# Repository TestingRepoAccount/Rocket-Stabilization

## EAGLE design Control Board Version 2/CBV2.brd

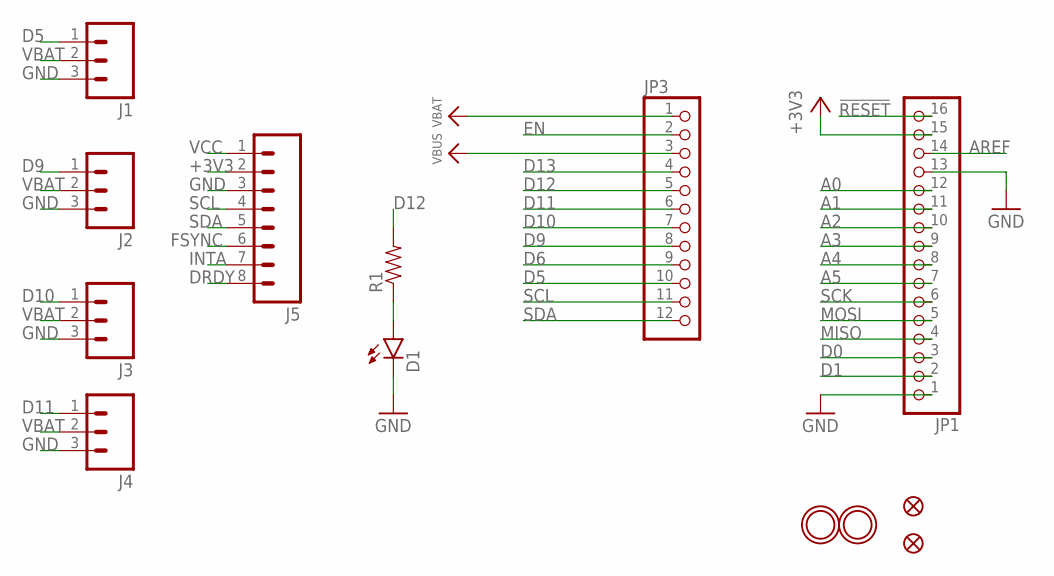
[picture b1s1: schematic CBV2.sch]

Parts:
D1: LED3MM
J1, J2, J3, J4: M03PTH; 1X03
J5: M08; 1X08_ROUND
JP1: HEADER-1X16ROUND; 1X16_ROUND
JP3: HEADER-1X12; 1X12_ROUND
R1: RESISTORPTH-1/4W; AXIAL-0.4
U$31, U$32: MOUNTINGHOLE2.5; MOUNTINGHOLE_2.5_PLATED
U$34, U$35: FIDUCIAL""; FIDUCIAL_1MM

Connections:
!RESET: JP1.16
+3V3: J5.2, JP1.15
A0: JP1.12
A1: JP1.11
A2: JP1.10
A3: JP1.9
A4: JP1.8
A5: JP1.7
AREF: JP1.14
D0: JP1.3
D1: JP1.2
D5: J1.1, JP3.10
D6: JP3.9
D9: J2.1, JP3.8
D10: J3.1, JP3.7
D11: J4.1, JP3.6
D12: JP3.5, R1.P$2 (2)
D13: JP3.4
DRDY: J5.8
EN: JP3.2
FSYNC: J5.6
GND: D1.K (C), J1.3, J2.3, J3.3, J4.3, J5.3, JP1.1, JP1.13
INTA: J5.7
MISO: JP1.4
MOSI: JP1.5
unnamed: D1.A, R1.P$1 (1)
SCK: JP1.6
SCL: J5.4, JP3.11
SDA: J5.5, JP3.12
VBAT: J1.2, J2.2, J3.2, J4.2, JP3.1
VBUS: JP3.3
VCC: J5.1

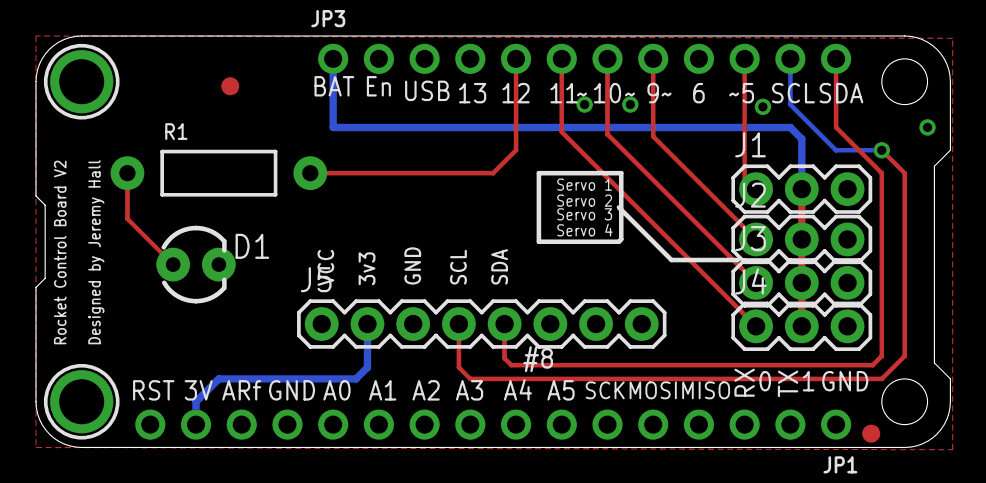
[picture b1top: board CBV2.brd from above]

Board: 2 copper layers, 50.8 x 22.9 mm, 13 parts (0 on the bottom side), 11 nets.

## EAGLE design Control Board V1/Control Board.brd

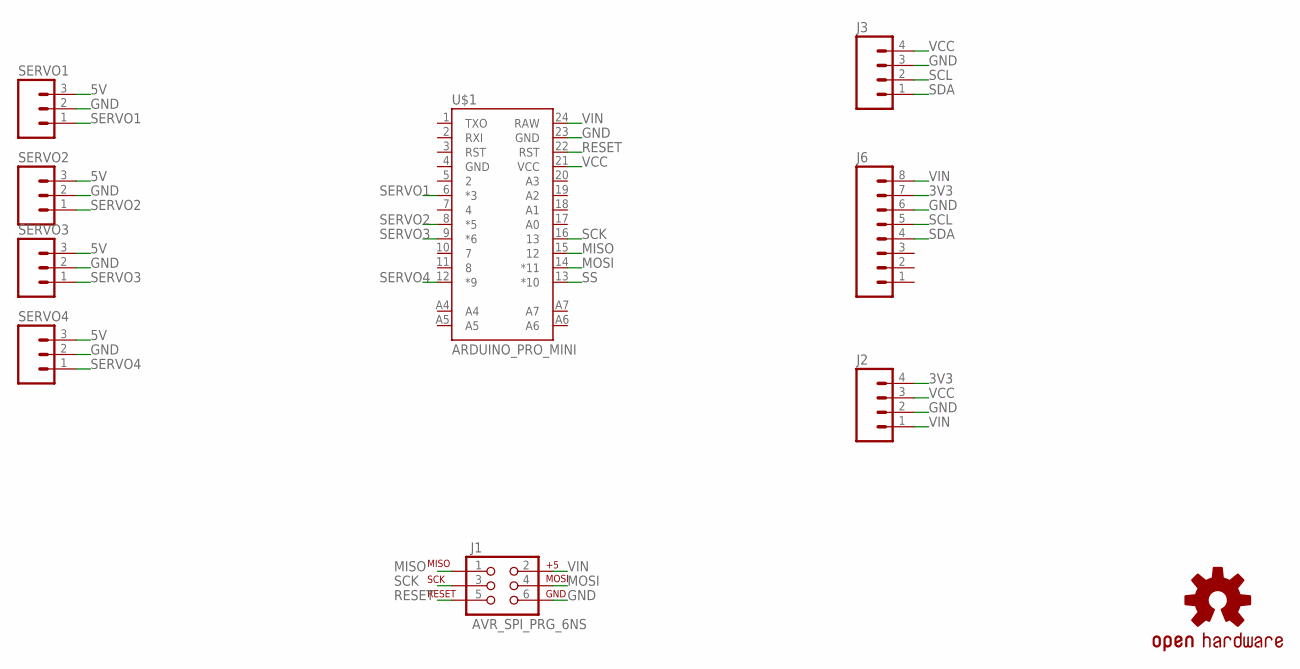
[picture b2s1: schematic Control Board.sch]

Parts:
J1: AVR_SPI_PRG_6NS; 2X3-NS
J2, J3: M04PTH; 1X04
J6: M08; 1X08_ROUND
LOGO1: OSHW-LOGOM-COPPER; OSHW-LOGO-M_COPPER
SERVO1, SERVO2, SERVO3, SERVO4: M03PTH; 1X03
U$1: ARDUINO_PRO_MINI

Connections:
3V3: J2.4, J6.7
5V: SERVO1.3, SERVO2.3, SERVO3.3, SERVO4.3
GND: J1.6, J2.2, J3.3, J6.6, SERVO1.2, SERVO2.2, SERVO3.2, SERVO4.2, U$1.23 (GND)
MISO: J1.1, U$1.15 (12)
MOSI: J1.4, U$1.14 (*11)
RESET: J1.5, U$1.22 (RST)
SCK: J1.3, U$1.16 (13)
SCL: J3.2, J6.5
SDA: J3.1, J6.4
SERVO1: SERVO1.1, U$1.6 (*3)
SERVO2: SERVO2.1, U$1.8 (*5)
SERVO3: SERVO3.1, U$1.9 (*6)
SERVO4: SERVO4.1, U$1.12 (*9)
SS: U$1.13 (*10)
VCC: J2.3, J3.4, U$1.21 (VCC)
VIN: J1.2, J2.1, J6.8, U$1.24 (RAW)

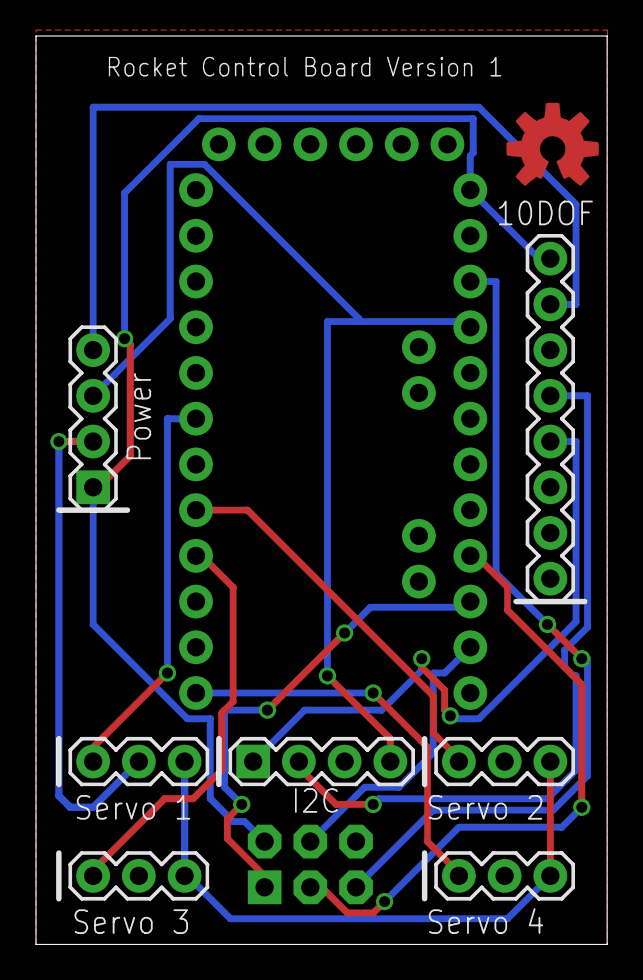
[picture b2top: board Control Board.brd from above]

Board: 2 copper layers, 31.7 x 50.5 mm, 10 parts (0 on the bottom side), 15 nets.

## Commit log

2016-05-29 First Commit
    Add base 9Dof Code!
2016-07-31 Add Version 1 of rocket stabilization code
2016-08-03 Add Barometic Functions based on Adafruit BMP085 Library
2016-08-04 Add SD Logging and added more functions for future functionality
2016-08-09 SD Logging now enabled and working properly
2016-08-20 Rocket Stabilization V1.9
    Added Preliminary Abort Sequences and Full Datalogging capabilities.
2016-09-09 Added Control Board and Schematic
2016-09-17 Abort Functional
    Abort bugs are fixed and are ready to go
2016-11-28 Add Version 2
    Added Version 2 of the control board and renamed the file for Version 1
2016-12-11 Add CAD PDF's
2017-03-28 Add Rocket Config file 1.0.0
2017-03-30 Updated Code
    Flight Ready(almost)
2017-03-30 Added Server and Client Control
2017-04-02 Updated Server, Client, and Flight Computer code
2017-04-02 Full working code
2017-07-11 Update to new code
    1.9 Updates
2018-01-26 Sure

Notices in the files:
parts and their libraries:
SparkFun-Boards: Licensing: Creative Commons ShareAlike 4.0 International - https://creativecommons.org/licenses/by-sa/4.0
microbuilder: This work is placed in the public domain, and may be freely used for commercial and non-commercial work with the following conditions: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
